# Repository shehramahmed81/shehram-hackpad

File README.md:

# Ordinary-Pad

A custom 12-key macropad with an OLED display, rotary encoder, and 3D printed case.

## Images

### Assembled Model

### PCB Layout

### Schematic

### PCB 3D View

### Case 3D View

## Features

* 12 MX-style switches
* 1 EC11 rotary encoder
* 1 0.91 inch OLED display
* Seeed Studio XIAO RP2040 microcontroller
* 3D printed case and lid
* Custom KiCad PCB
* KMK/CircuitPython firmware
* OLED connected using female-to-female Dupont jumper wires

## CAD

The case was designed as a two-part 3D printed enclosure:

* Bottom case/tray
* Top lid/plate

The CAD files are included in the `CAD/` folder.

Included CAD files:

* `Case.step`
* `Lid.step`
* `Macropad_Assembly.step`

## PCB

The PCB was designed in KiCad. It uses a 3 row by 4 column switch matrix with 1N4148 diodes.

The PCB files are included in the `PCB/` folder.

Included PCB files:

* KiCad schematic file
* KiCad PCB layout file

The production files are included in the `production/` folder.

Included production files:

* `gerbers.zip`

## Firmware

The firmware is written for KMK/CircuitPython and is included in the `Firmware/` folder.

Main firmware file:

* `code.py`

Pin mapping:

Rows:

* ROW0 = D0
* ROW1 = D1
* ROW2 = D2

Columns:

* COL0 = D3
* COL1 = D6
* COL2 = D7
* COL3 = D8

Rotary encoder:

* A = D9
* B = D10
* C = GND

OLED:

* SDA = D4
* SCL = D5
* VCC = 3V3
* GND = GND

## BOM

| Part                                 | Quantity |
| ------------------------------------ | -------- |
| Seeed Studio XIAO RP2040             | 1        |
| MX-style switches                    | 12       |
| 1N4148 diodes                        | 12       |
| EC11 rotary encoder                  | 1        |
| 0.91 inch OLED display               | 1        |
| Female-to-female Dupont jumper wires | 4        |
| M3 screws                            | 6        |
| M3 heat-set inserts                  | 6        |
| 3D printed case                      | 1        |
| 3D printed lid                       | 1        |

## Notes

The OLED is connected with female-to-female Dupont jumper wires instead of being mounted directly over the PCB header. This allows the OLED screen to be positioned in a cleaner location on the lid.

The case and lid are designed to be entirely 3D printed.

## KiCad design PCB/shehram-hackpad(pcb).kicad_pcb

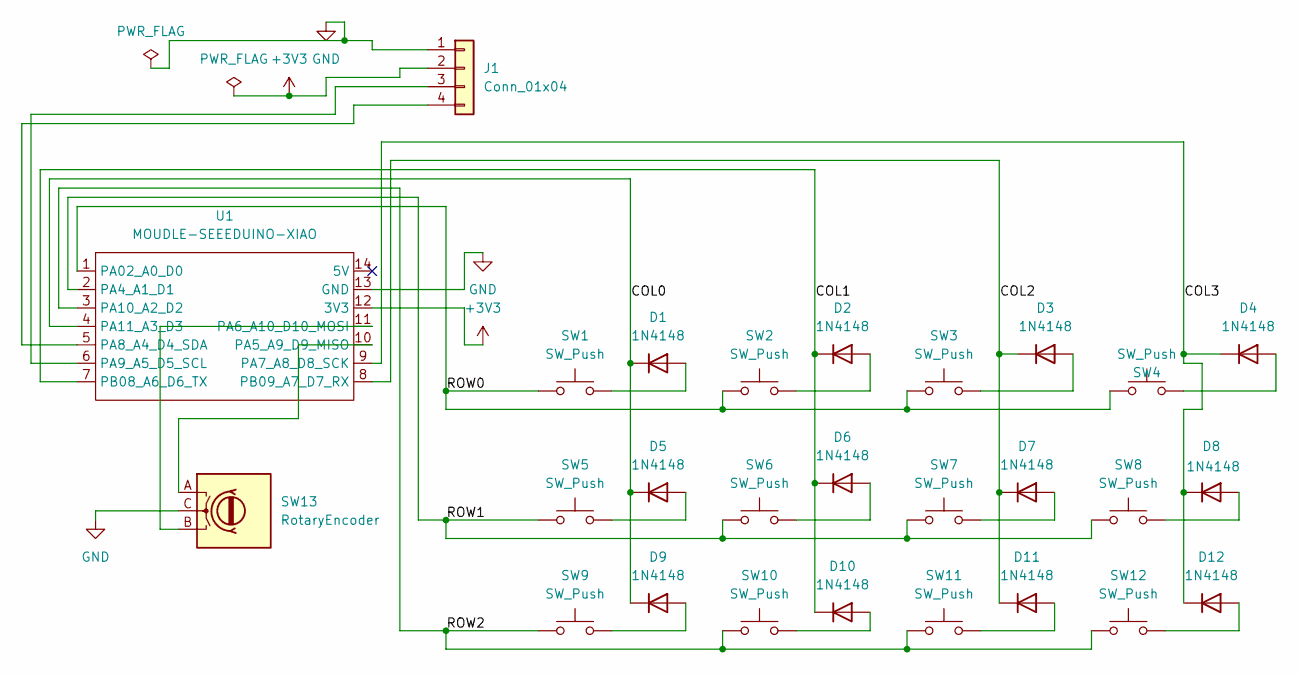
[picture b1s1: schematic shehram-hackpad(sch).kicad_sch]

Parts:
D1, D2, D3, D4, D5, D6, D7, D8, D9, D10, D11, D12: 1N4148; D_DO-35_SOD27_P7.62mm_Horizontal
J1: Conn_01x04; PinHeader_1x04_P2.54mm_Vertical
SW1, SW2, SW3, SW4, SW5, SW6, SW7, SW8, SW9, SW10, SW11, SW12: SW_Push; SW_Cherry_MX_1.00u_PCB
SW13: RotaryEncoder; RotaryEncoder_Alps_EC11E-Switch_Vertical_H20mm
U1: MOUDLE-SEEEDUINO-XIAO; XIAO-Generic-Hybrid-14P-2.54-21X17.8MM

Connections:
+3V3: J1.2, U1.12 (3V3)
/COL0: D1.1 (K), D5.1 (K), D9.1 (K), U1.4 (PA11_A3_D3)
/COL1: D2.1 (K), D6.1 (K), D10.1 (K), U1.7 (PB08_A6_D6_TX)
/COL2: D3.1 (K), D7.1 (K), D11.1 (K), U1.8 (PB09_A7_D7_RX)
/COL3: D4.1 (K), D8.1 (K), D12.1 (K), U1.9 (PA7_A8_D8_SCK)
/ROW0: SW1.1, SW2.1, SW3.1, SW4.1, U1.1 (PA02_A0_D0)
/ROW1: SW5.1, SW6.1, SW7.1, SW8.1, U1.2 (PA4_A1_D1)
/ROW2: SW9.1, SW10.1, SW11.1, SW12.1, U1.3 (PA10_A2_D2)
GND: J1.1, SW13.C, U1.13 (GND)
unnamed: D1.2 (A), SW1.2
unnamed: D2.2 (A), SW2.2
unnamed: D3.2 (A), SW3.2
unnamed: D4.2 (A), SW4.2
unnamed: D5.2 (A), SW5.2
unnamed: D6.2 (A), SW6.2
unnamed: D7.2 (A), SW7.2
unnamed: D8.2 (A), SW8.2
unnamed: D9.2 (A), SW9.2
unnamed: D10.2 (A), SW10.2
unnamed: D11.2 (A), SW11.2
unnamed: D12.2 (A), SW12.2
unnamed: J1.3, U1.6 (PA9_A5_D5_SCL)
unnamed: J1.4, U1.5 (PA8_A4_D4_SDA)
unnamed: SW13.A, U1.10 (PA5_A9_D9_MISO)
unnamed: SW13.B, U1.11 (PA6_A10_D10_MOSI)

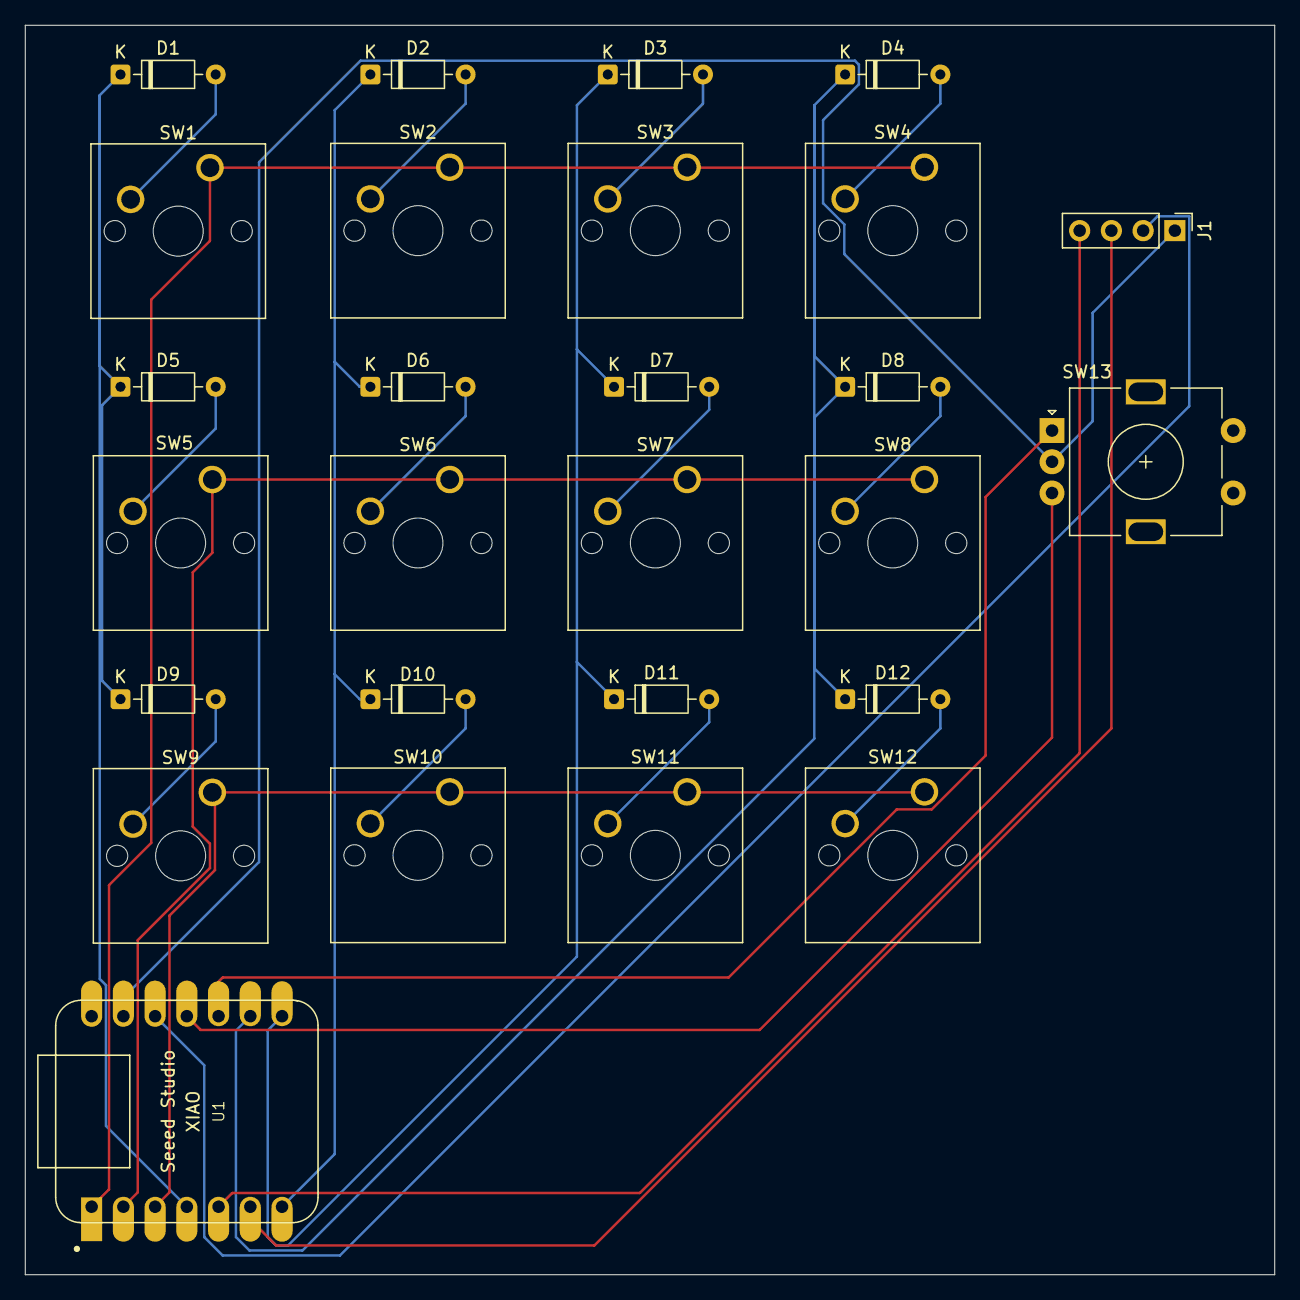
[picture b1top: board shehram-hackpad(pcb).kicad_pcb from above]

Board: 2 copper layers, 100.0 x 100.0 mm, 27 parts (0 on the bottom side), 25 nets.
